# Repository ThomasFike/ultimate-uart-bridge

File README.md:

# ultimate-uart-bridge

My project to make the ultimate usb to uart bridge

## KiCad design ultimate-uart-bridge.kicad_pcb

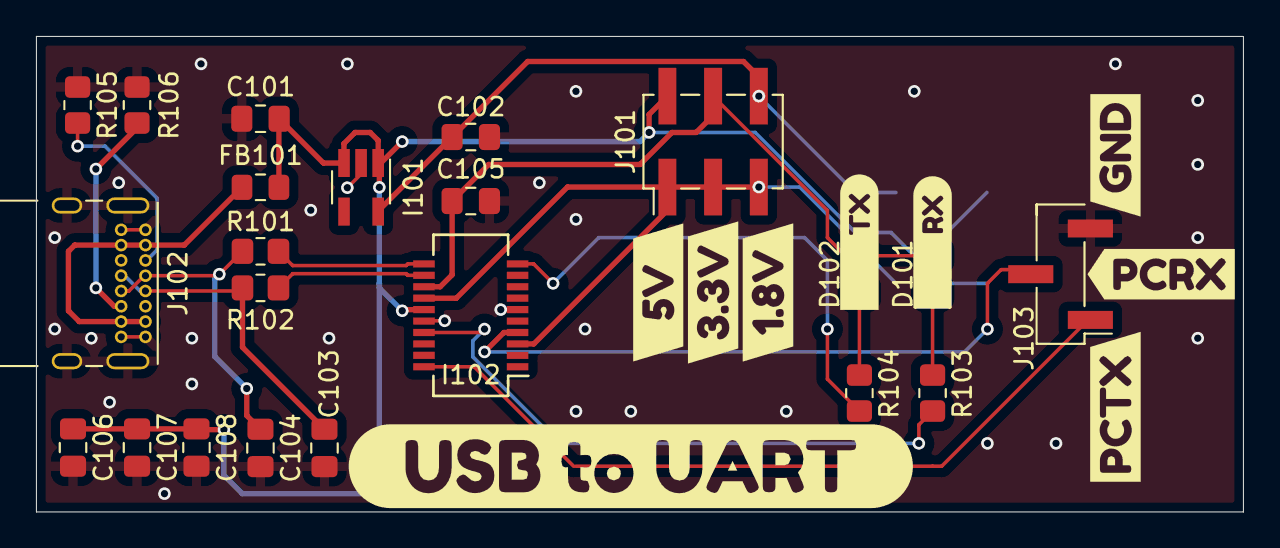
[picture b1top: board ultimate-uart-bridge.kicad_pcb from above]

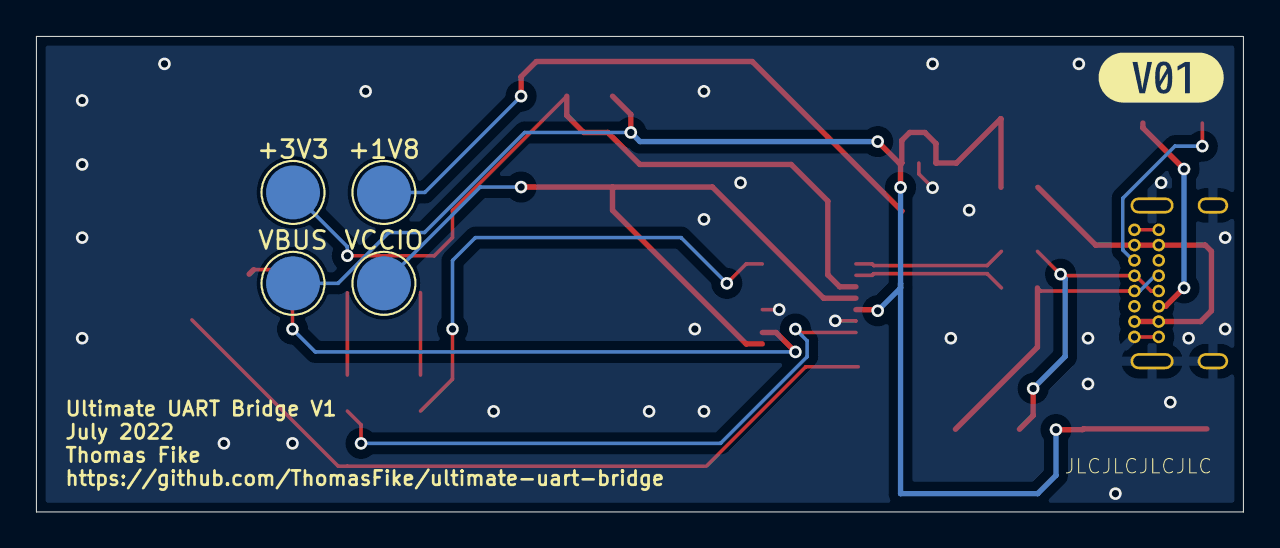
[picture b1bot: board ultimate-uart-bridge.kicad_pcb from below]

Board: 2 copper layers, 67.1 x 26.4 mm, 36 parts (5 on the bottom side), 18 nets.

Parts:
+1V8, +3V3: TestPoint; TestPoint_Pad_D3.0mm
C101, C102: 1uF; C_0805_2012Metric_Pad1.18x1.45mm_HandSolder
C103, C104: 47pF; C_0805_2012Metric_Pad1.18x1.45mm_HandSolder
C105, C107: 100nF; C_0805_2012Metric_Pad1.18x1.45mm_HandSolder
C106: 10nF; C_0805_2012Metric_Pad1.18x1.45mm_HandSolder
C108: 4.7uF; C_0805_2012Metric_Pad1.18x1.45mm_HandSolder
D101, D102: LED; LED_0805_2012Metric_Pad1.15x1.40mm_HandSolder
FB101: Ferrite_Bead_Small; L_0805_2012Metric_Pad1.15x1.40mm_HandSolder
I101: MIC5317-1.8YM5-TR; SOT-23-5_HandSoldering
I102: FT231XS; SSOP-20_3.9x8.7mm_P0.635mm
J101: Conn_02x03_Row_Letter_First; PinHeader_2x03_P2.54mm_Vertical_SMD
J102: USB_C_Receptacle_USB2.0; USB_C_Receptacle_GCT_USB4085
J103: Conn_01x03; PinHeader_1x03_P2.54mm_Vertical_SMD_Pin1Left
R101, R102: 27; R_0805_2012Metric_Pad1.20x1.40mm_HandSolder
R103, R104: R; R_0805_2012Metric_Pad1.20x1.40mm_HandSolder
R105, R106: 5.1k; R_0805_2012Metric_Pad1.20x1.40mm_HandSolder
VBUS: TestPoint; TestPoint_Pad_D3.0mm
VCCIO: TestPoint; TestPoint_Pad_D3.0mm
kibuzzard-62CBA0C9: G***; kibuzzard-62CBA0C9
kibuzzard-62CBA9F2: G***; kibuzzard-62CBA9F2
kibuzzard-62CBA40F: G***; kibuzzard-62CBA40F
kibuzzard-62CBA051: G***; kibuzzard-62CBA051
kibuzzard-62CBA130: G***; kibuzzard-62CBA130
kibuzzard-62CBA316: G***; kibuzzard-62CBA316
kibuzzard-62CBA331: G***; kibuzzard-62CBA331
kibuzzard-62CBA409: G***; kibuzzard-62CBA409
kibuzzard-62CBA429: G***; kibuzzard-62CBA429
kibuzzard-62D45EE7: G***; kibuzzard-62D45EE7

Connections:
+1V8: +1V8.1, C102.1, I101.5 (VOUT), J101.6
+3V3: +3V3.1, C105.2, D101.2 (A), D102.2 (A), I102.13 (3V3OUT), J101.4
/PCRX: I102.4 (RXD), J103.2
/PCTX: I102.20 (TXD), J103.1
/RXLED#: I102.17 (CBUS1), R103.2
/TXLED#: I102.10 (CBUS2), R104.2
GND: C101.2, C102.2, C103.2, C104.2, C105.1, C106.2, C107.2, C108.2, I101.2 (GND), I102.6 (GND), I102.16 (GND), J102.A1 (GND), J102.A12 (GND), J102.B1 (GND), J102.B12 (GND), J102.S1 (SHIELD), J103.3, R105.1, R106.2
unnamed: C103.1, J102.A7 (D-), J102.B7 (D-), R102.1
unnamed: C104.1, J102.A6 (D+), J102.B6 (D+), R101.1
unnamed: D101.1 (K), R103.1
unnamed: D102.1 (K), R104.1
unnamed: FB101.2, J102.A4 (VBUS), J102.A9 (VBUS), J102.B4 (VBUS), J102.B9 (VBUS)
unnamed: J102.A5 (CC1), R105.2
unnamed: J102.B5 (CC2), R106.1
USBD_N: I102.12 (USBDM), R102.2
USBD_P: I102.11 (USBDP), R101.2
VBUS: C101.1, C106.1, C107.1, C108.1, FB101.1, I101.1 (VIN), I101.3 (EN), I102.15 (VCC), J101.2, VBUS.1
VCCIO: I102.3 (VCCIO), I102.14 (~RESET), J101.1, J101.3, J101.5, VCCIO.1

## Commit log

2021-07-25 Add project description
2021-07-25 Add kicad project
    Adding the empty kicad project for this project.
2021-12-18 Adding Old Work
2021-12-18 First Routing
2022-05-26 Change Switch Circuit
2022-05-26 Update Ferrite Bead
2022-07-11 Update .gitignore for Kicad 6
2022-07-11 New inital routing
2022-07-11 GND stiching
2022-07-17 Add testpoints and text
2022-07-17 Update Production Files
2022-09-19 New stuff
